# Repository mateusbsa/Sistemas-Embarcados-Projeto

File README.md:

# Sistemas Embarcados - 2021.2

#### Análise da temperatura e umidade do solo/ar.

### 1 - Descrição do projeto:

##### O projeto consiste na criação de um dispositivo capaz de coletar dados referentes a temperatura e umidade do ar, como também a umidade do solo, a fim de se poder realizar análises onde o sistema tenha sido instalado.

### 2 - Objetivos

  O objetivo do projeto é coletar os dados dos sensores de temperatura e umidade do ar e umidade do solo, onde serão enviados através de conexão wireless para o Adafruit.IO, um sistema de armazenamento em nuvem, com a capcidade de exibir dados em tempo real enquanto online, realizar a leitura, o monitoramento e o controle de dados que estão sendo recebidos.
  
### 3 - Resumo das arquiteturas e seus fluxogramas

   1.  Hardware

   * Protótipo real 

     - **ESP8266**: micro chip WiFi com pilha TCP (Transfer Control Protocol)/IP(Internet Protocol) completa e capacidade microcontroladora produzida pela empresa chinesa Espressif Systems. O chip ESP8266 é combinado com um conector micro-USB (Universal Serial Bus) com interface USB-Serial para acoplamento a computadores, um regulador de tensão para 3.3 V e um conversor analógico-digital para compor a placa NodeMCU.
     - **DHT11**: é um sensor de temperatura e umidade que permite medir temperaturas de 0 a 50 graus Celsius e umidade na faixa de 0% a 90%, com faixa de precisão de 2 graus para temperatura e 5% para umidade. Tal sensor ainda conta com um controlador de 8 bits que converte os sinais de temperatura e umidade captados em um sinal serial que pode, por sua vez, ser enviado para um microcontrolador através de seu pino de dados.

   * Diagrama de Blocos do Hardware

  2.  Firmware
  
  * Fluxograma do Firmware

  3.  Software/App
  
  * **ADAFRUIT.IO**: é um sistema de armazenamento em nuvem, com esse serviço é possível exibir dados em tempo real enquanto online, realizar a leitura, o monitoramento e o controle de dados que estão sendo recebidos e transmitidos, além da possibilidade de enviar esses dados para sites e redes sociais como o Twitter. A ferramenta é gratuita e está disponível para uso no site: https://io.adafruit.com/.
  
  * Fluxograma do APP

### 4 - Resumo dos Resultados

Através desse projeto conseguimos realizar as seguintes etapas:

* HARDWARE:
  
  <p> :heavy_check_mark: Esquema Elétrico <p> 

  <p> :heavy_check_mark: Layout PCB

  <p> :heavy_check_mark: PCB 3D

  <p> :heavy_check_mark: CASE

* Firmware 
    <p> :heavy_check_mark:  Criação de uma biblioteca responsável pela leituras dos sensores:
      
    - A pasta **lib** contém a nossa própria biblioteca(read_sensor_library), onde é reponsável pela leitura dos sensores.
    - Na pasta **scr** contém o código principal do projeto.

* App
   <p> :heavy_check_mark: Criação da parte visual para mostrar as leituras dos sensores (ADAFRUIT.IO)<p>

### 5 - Vídeos
  - Protótipo

  - Apresentação do projeto
    
### 6 - Grupo

* Mateus Barbosa
* Marcelo Filho
* Moabe Barbosa Alves

### 7 - Instituição

* Instituto Federal da Paraíba - IFPB
* Campus Campina Grande

### 8 - Docente responsável
* Alexandre Sales Vasconcelos

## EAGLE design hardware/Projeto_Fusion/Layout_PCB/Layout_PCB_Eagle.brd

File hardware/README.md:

# DESCRIÇÃO DE HARDWARE

### DIAGRAMA DE BLOCOS HARDWARE

* Protótipo real

* O microcontrolador ESP8266 é alimentado por uma bateria de 3.3V. No conector GPIO2 é conectado o sensor de umidade e temperatura DHT11 e no conector ADC0 é conectado o sensor de umidade do solo. 

### PROTOTIPAÇÃO DO HARDWARE FUSION/EAGLE

* Esquema Elétrico

* Layout PCB

* PCB 3D

* CASE

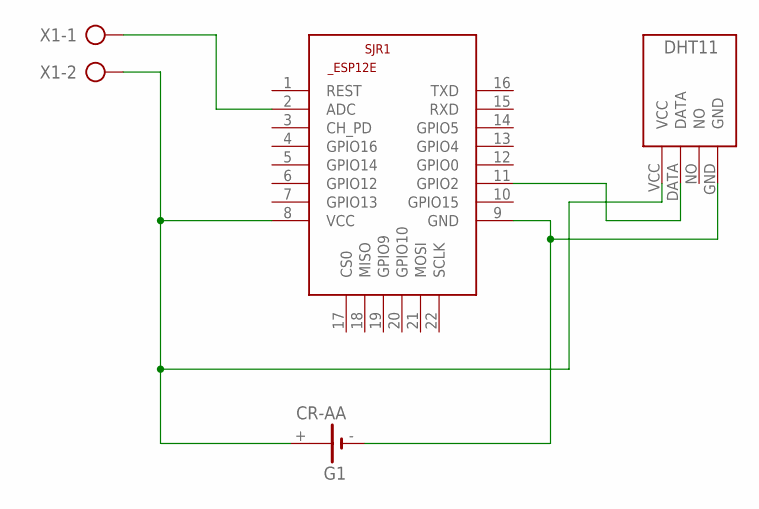
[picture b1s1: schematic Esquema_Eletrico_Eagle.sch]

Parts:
G1: CR-AA; CRAA
SJR1: ESP8266-12EESP12E; ESP8266-ESP12E
U$1: DHT11-PION.
X1: AK300/2

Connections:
unnamed: SJR1.2 (ADC), X1.1
unnamed: G1.+, SJR1.8 (VCC), U$1.VCC, X1.2
unnamed: SJR1.11 (GPIO2), U$1.DATA
unnamed: G1.-, SJR1.9 (GND), U$1.GND

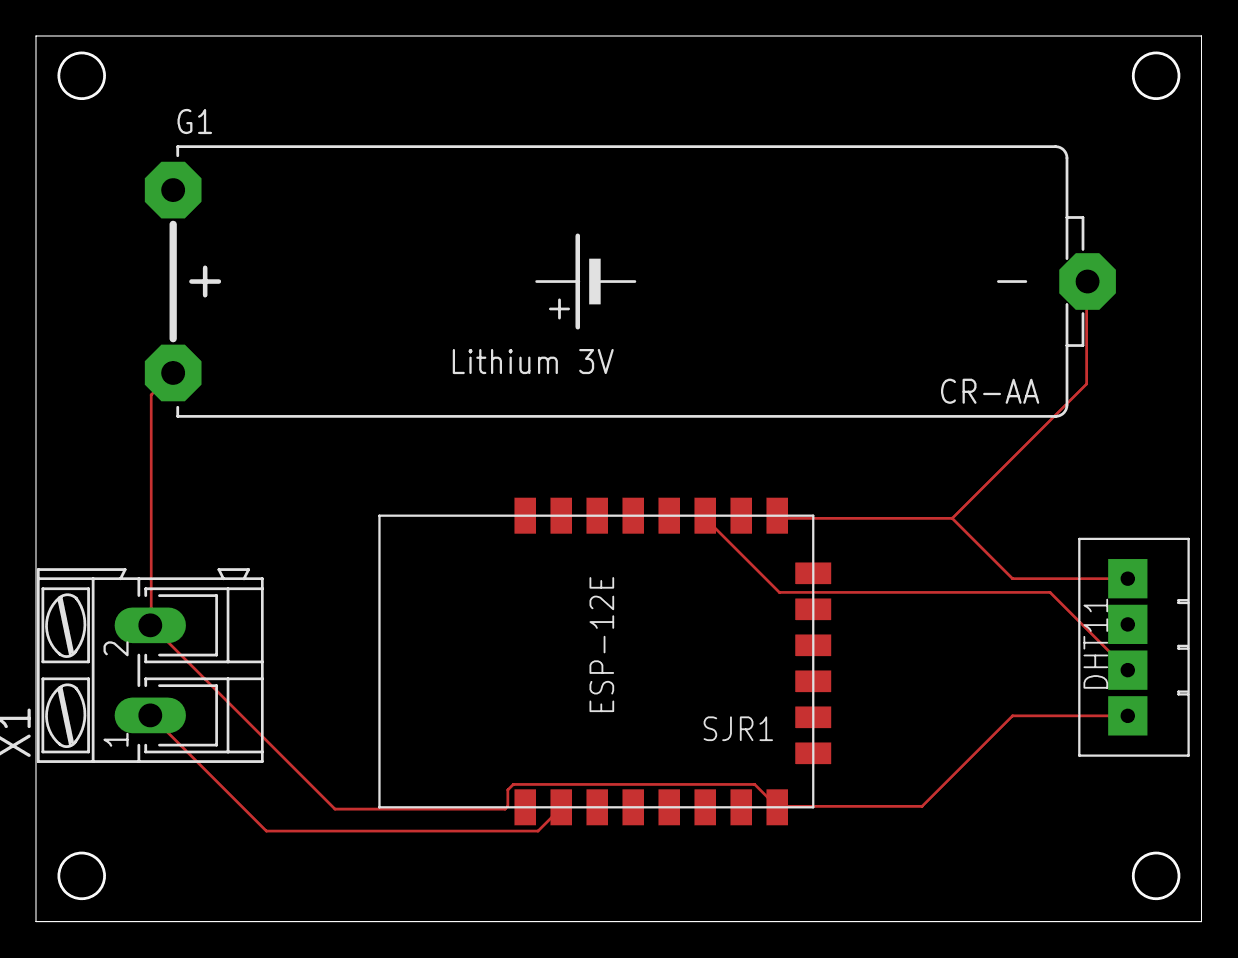
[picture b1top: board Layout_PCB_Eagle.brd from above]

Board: 2 copper layers, 64.6 x 49.0 mm, 4 parts (0 on the bottom side), 4 nets.

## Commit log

2021-11-28 Descrição-Projeto
2021-11-28 Docs
2022-02-20 Organização das pastas
2022-03-03 ajustes
2022-03-10 atualização app
2022-03-19 Adicionando Eagle_Fusion e códigos do projeto
2022-03-19 ajuste no diagrama
2022-03-19 ajuste no Diagrama_Blocos_Hardware.jpeg
2022-03-20 ajuste
2022-03-20 add AdafruitIO_App.jpeg
2022-03-20 AJUSTE DE IMAGEM
2022-03-20 Ajuste no Code/src/main/main.ino
2022-03-20 relatorio_final_do_projeto.pdf
2022-03-20 alteração no relatorio_final_do_projeto.pdf
2022-03-20 Add foto do protótipo_real
2022-03-20 adicionando apresentação.pdf
2022-03-20 atualização no relatorio_final_do_projeto
2022-03-20 ajuste relatorio_final_do_projeto
2022-03-20 Adicionando vídeo do funcionamento do prototipo
2022-03-20 Ajuste no codigo
